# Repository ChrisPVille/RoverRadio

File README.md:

# RoverRadio
Custom 50Mhz SDR radio for my rover project

Right now the plan is to use this radio along with liquid-dsp running on an ARM to create an embedded QAM/APSK (QAM with non-rectangular constellations) long range communication system situated in the 6m ham band.

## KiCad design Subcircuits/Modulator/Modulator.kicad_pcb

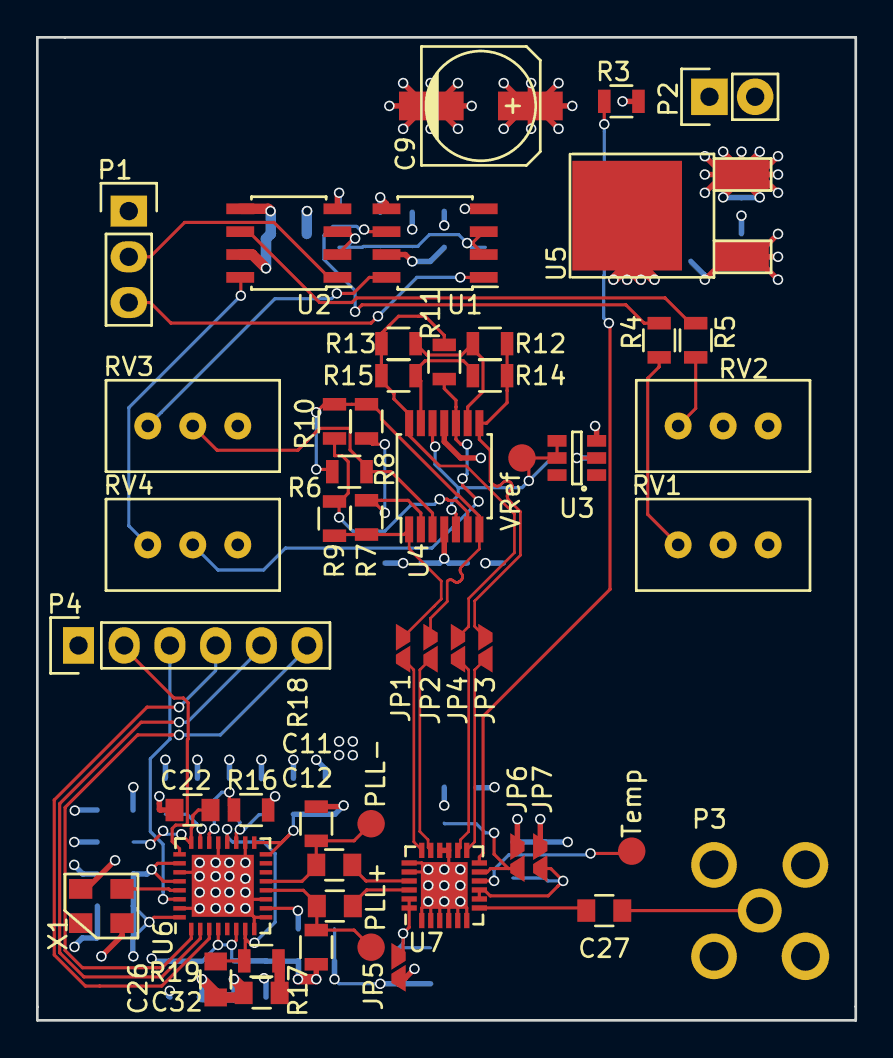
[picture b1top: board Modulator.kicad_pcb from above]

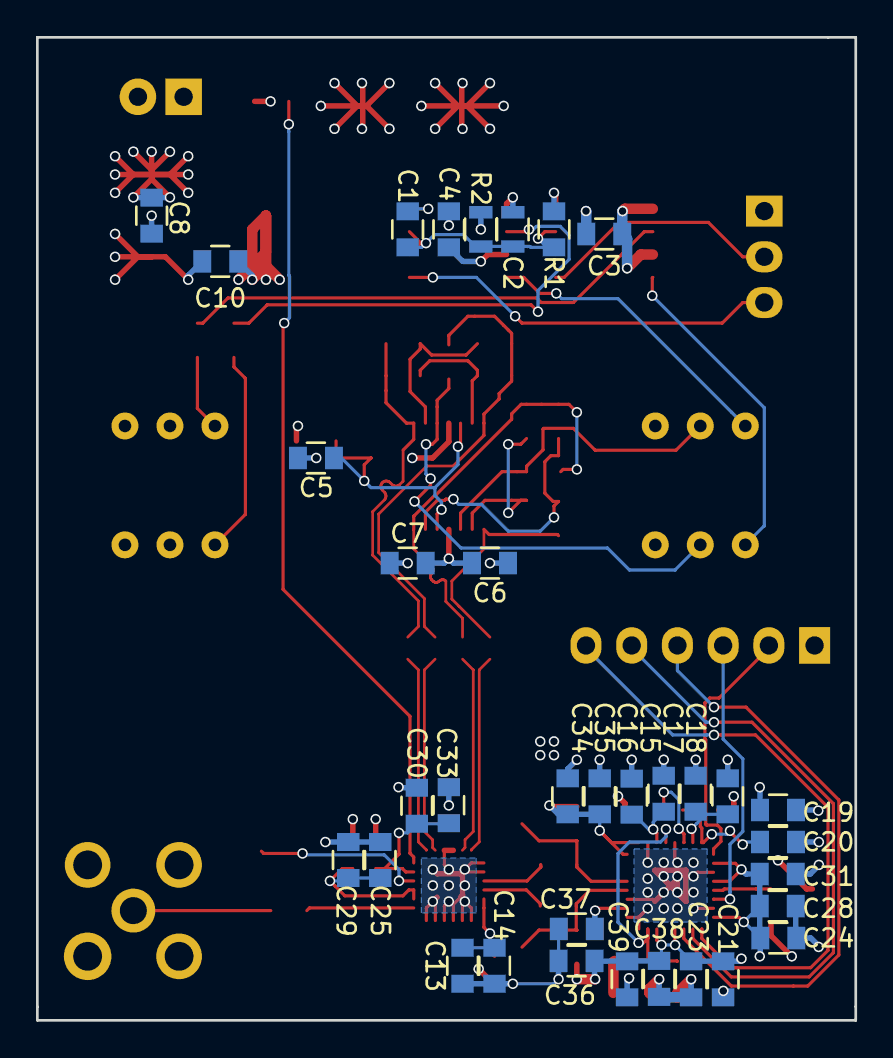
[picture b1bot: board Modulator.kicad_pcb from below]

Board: 4 copper layers, 45.5 x 54.6 mm, 85 parts (34 on the bottom side), 50 nets.

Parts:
C1, C2, C3, C4, C8, C13, C29, C33: 1u; C_0805
C5, C6, C7, C14, C16, C18, C21, C22, C24, C25, C27, C30, C31, C35, C37, C39: 0.1u; C_0805
C9: 100u; c_elec_6.3x5.8
C10: 10u; C_0805
C11, C12: 100p; C_0805
C15, C17, C19, C20, C23, C28, C34, C36, C38: 10p; C_0805
C26: 6.77n; C_0805
C32: 32.7n; C_0805
JP1, JP2, JP3, JP4, JP5, JP6, JP7: Jumper_NO_Small; SolderJump
P1: CONN_01X03; Pin_Header_Straight_1x03
P2: CONN_01X02; Pin_Header_Straight_1x02
P3: SMA; SMA-1814832
P4: CONN_01X06; Pin_Header_Straight_1x06
PLL+: TP; Measurement_Point_Round-SMD-Pad_Small
PLL-: TP; Measurement_Point_Round-SMD-Pad_Small
R1: 2.49k; R_0805
R2: 1.65k; R_0805
R3, R6, R11: 10k; R_0805
R4, R5: 5k; R_0805
R7, R8, R9, R10, R12, R13, R14, R15: 2.2k; R_0805
R16: 5.1k; R_0805
R17, R18: 50; R_0805
R19: 11.8k; R_0805
RV1, RV2, RV3, RV4: 20k; PV36W
Temp: TP; Measurement_Point_Round-SMD-Pad_Small
U1, U2: LTC1569-7; SOIC-8_3.9x4.9mm_Pitch1.27mm
U3: ADR130; SOT-23-6
U4: LMV324; TSSOP-14_4.4x5mm_Pitch0.65mm
U5: LD1117DT33TR; TO-252-2Lead
U6: ADF4351; QFN-32-1EP_5x5mm_Pitch0.5mm
U7: ADL5385; QFN-24-1EP_4x4mm_Pitch0.5mm
VRef: TP; Measurement_Point_Round-SMD-Pad_Small
X1: ASTX-H11

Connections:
+3V3: C10.1, C19.1, C21.1, C23.1, C24.1, C28.1, C31.1, C34.1, C35.1, C36.1, C37.1, C38.1, C39.1, R17.1, R18.1, U5.2, U6.4, U6.6, U6.10, U6.16, U6.17, U6.26, U6.28, U6.32, X1.4
+5V: C3.1, C4.1, C6.2, C7.2, C8.1, C9.1, JP5.1, JP6.2, JP7.2, P2.2, R1.1, RV1.2, RV2.2, U1.5, U1.7, U2.5, U2.7, U3.3, U4.4, U5.3
/PLL_N: C12.1, U7.22
/PLL_P: C11.1, U7.21
/pI_N: JP4.1, R11.1, R13.1, R15.1, U4.14
/pI_P: JP3.1, R12.1, R14.1, U4.8
/pQ_N: JP2.1, R6.1, R8.1, R10.1, U4.7
/pQ_P: JP1.1, R7.1, R9.1, U4.1
GND: C1.2, C2.2, C3.2, C4.2, C5.2, C6.1, C7.1, C8.2, C9.2, C10.2, C13.1, C14.1, C15.2, C16.2, C17.2, C18.2, C19.2, C20.2, C21.2, C22.2, C23.2, C24.2, C25.1, C26.2, C28.2, C29.1, C30.1, C31.2, C32.2, C33.1, C34.2, C35.2, C36.2, C37.2, C38.2, C39.2, P1.1, P2.1, P3.2, P4.1, R2.2, R3.2, R16.2, RV3.3, RV4.3, U1.4, U2.4, U3.2, U4.11, U5.1, U6.8, U6.9, U6.11, U6.18, U6.21, U6.27, U6.31, U6.33, U7.1, U7.2, U7.3, U7.4, U7.5, U7.6, U7.15, U7.16, U7.19, U7.20, U7.25, X1.2
I_N: JP4.2, U7.14
I_P: JP3.2, U7.13
unnamed: C1.1, C2.1, R1.2, R2.1, U1.2, U1.3, U2.2, U2.3
unnamed: C13.2, C14.2, JP5.2, U7.23, U7.24
unnamed: C15.1, C16.1, U6.19
unnamed: C17.1, C18.1, U6.23
unnamed: C20.1, C22.1, U6.24
unnamed: C25.2, C29.2, JP7.1, U7.8, U7.9
unnamed: C26.1, R19.1, U6.7, U6.20
unnamed: C27.1, P3.1
unnamed: C27.2, U7.7
unnamed: C30.2, C33.2, JP6.1, U7.11
unnamed: C32.1, R19.2
unnamed: P1.2, U2.1
unnamed: P1.3, U1.1
unnamed: R4.1, RV1.1
unnamed: R4.2, U1.6
unnamed: R5.1, RV2.1
unnamed: R5.2, U2.6
unnamed: R6.2, RV3.2, U4.3
unnamed: R7.2, R8.2, U4.2
unnamed: R9.2, R10.2, U4.6
unnamed: R11.2, RV4.2, U4.10
unnamed: R12.2, R13.2, U4.9
unnamed: R14.2, R15.2, U4.13
unnamed: R16.1, U6.22
unnamed: RV3.1, U1.8
unnamed: RV4.1, U2.8
unnamed: U6.29, X1.3
unnamed: Temp.1, U7.10
PLLClkIn: P4.6, U6.1
PLLDataIn: P4.5, U6.2
PLLLe: P4.4, U6.3
PLLLock: P4.2, U6.25
PLLMuxOut: P4.3, U6.30
PLLOut_N: C11.2, PLL-.1, R18.2, U6.13
PLLOut_P: C12.2, PLL+.1, R17.2, U6.12
Q_N: JP2.2, U7.17
Q_P: JP1.2, U7.18
Tx_En: R3.1, U7.12
Vref: C5.1, U3.4, U3.5, U4.5, U4.12, VRef.1

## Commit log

2015-09-13 Started the modulator
2015-09-13 Updated modulator
2015-09-18 Organized folders
2015-09-19 Cleaned up components library
2015-09-19 Updated Schematic
2015-09-19 Updated datasheets
2015-09-20 More modifications to the schematics
2015-09-21 Moar schematics!
2015-09-21 Made IQ LPF cutoff adjustable
2015-09-24 Added footprints needed
2015-09-24 Finished modulator schematic
2015-09-24 Annotated and PDFed modulator schematic
2015-09-25 Finished prototype modulator board
2015-09-25 Modulator gerbers added
2015-09-25 Removed backup files from tree
